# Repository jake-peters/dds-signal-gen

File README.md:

# DDS Signal Generator using AD9834

A signal generator designed around Analog Devices AD9834 DDS chip capable of outputting sinusoidal, triangle and square waves. Output filtering with a 9th order Elliptic filter or 7th order Linear Phase filter. PCB designed in KiCad 6.

V2 version includes update to correct orientation issue with latching relays.

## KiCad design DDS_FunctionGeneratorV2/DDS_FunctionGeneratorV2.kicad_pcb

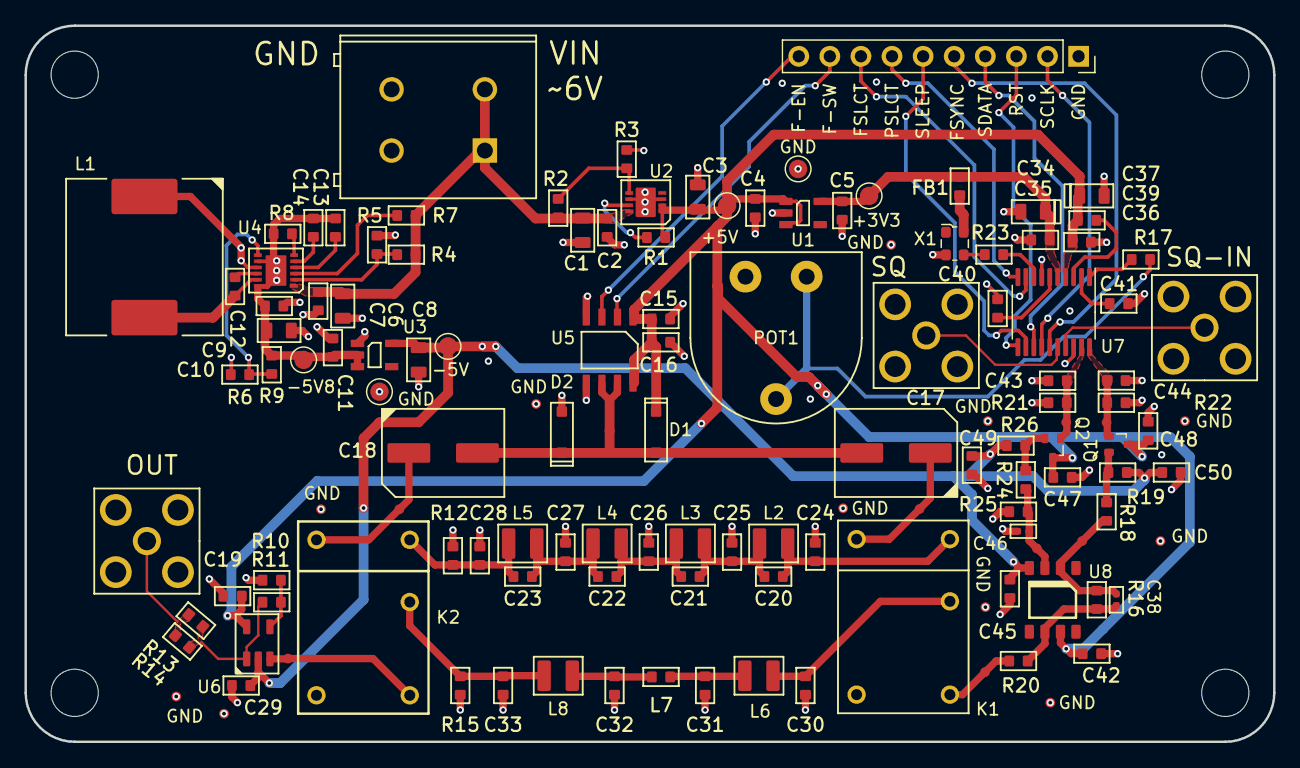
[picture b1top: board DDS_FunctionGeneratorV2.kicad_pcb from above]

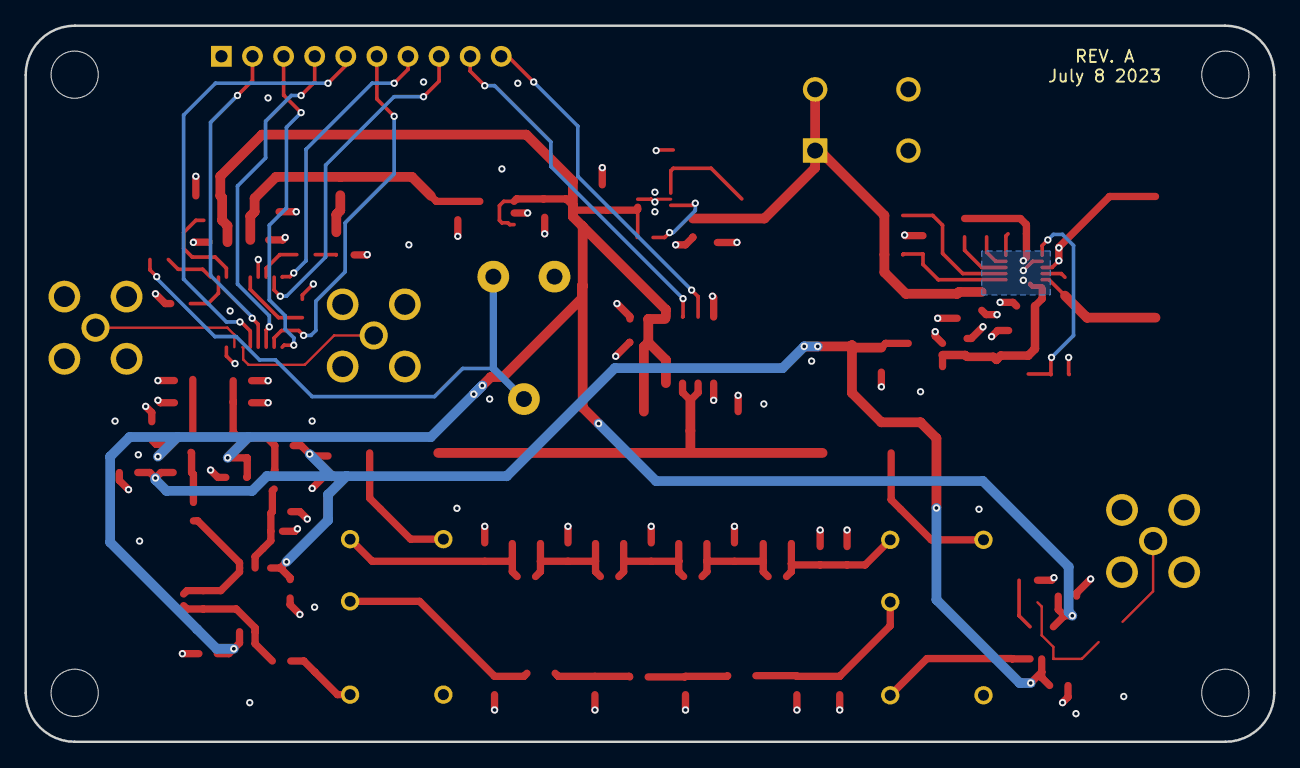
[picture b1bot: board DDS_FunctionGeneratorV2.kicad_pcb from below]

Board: 4 copper layers, 102.0 x 58.5 mm, 137 parts (2 on the bottom side), 59 nets.

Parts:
C1, C3, C6, C8, C10: CAP_0805; SMD_0805
C2, C4, C5, C7, C9, C11, C12, C13, C14, C15, C16, C19, C20, C21, C22, C23, C24, C25, C26, C27, C28, C29, C30, C31, C32, C33, C35, C36, C39, C40, C41, C42, C43, C44, C45, C47, C48, C49, C50: CAP_0603; SMD_0603
C17, C18: 865080345010
C34, C37: CAP_POL_0805; SMD_POL_0805
C38, C46: CAP_0402; SMD_0402
D1, D2: 1N4148W-E3-18; SOD-123
FB1: BEAD_0603; SMD_0603
H1, H2, H3, H4: 0.152_IN_DIA; 0.152_IN_DIA-6-32
J1: 691411410002
J2, J3, J5: SMA_CONN_TH
J4: HEADER_01X10; PinSocket_1x10_P2.54mm_Vertical
K1, K2: DS1E-SL-DC5V
L1: 7447715330
L2, L3, L4, L5, L6, L8: IND_1008; SMD_1008
L7: IND_0603; SMD_0603
POT1: PTN10-E200HB20
Q1, Q2: BFR182W; SOT323_BFR182W
R1, R2, R3, R4, R5, R6, R7, R8, R9, R10, R11, R12, R13, R14, R15, R16, R17, R18, R19, R20, R21, R22, R23, R24, R25, R26: RES_0603; SMD_0603
TP1, TP2, TP3, TP4, TP5, TP6: TestPoint_2.0mm_PAD; TestPoint_Pad_D1.5mm
TP7, TP8, TP9, TP11, TP12, TP13, TP14, TP15, TP16, TP17, TP18, TP20, TP21, TP22, TP23, TP24, TP25, TP26, TP27, TP28, TP29: TestPoint_2.0mm_PAD; TestPoint_Pad_D0.8mm
U1: ADP151AUJZ; TSOT_5Pin
U2: ADP7102; LFCSP_WD_8Pin
U3: ADP7182AUJZ; TSOT_5Pin
U4: MAX17580ATC+; TDFN-EP_12Pin
U5: MCP14A0602-E/SN; SOIC_8Pin
U6: LT1815IS5; TSOT-23_S5-Package
U7: AD9834; TSSOP-20_4.4x6.5mm_P0.65mm
U8: LT1818IS8; S8_Package_LT1818
X1: ECS-TXO-2520MV-500-AY-TR; Oscillator_SMD_ECS_2520MV-xxx-xx-4Pin_2.5x2.0mm

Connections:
+3V3: C5.1, C34.1, C35.2, FB1.1, TP2.1, U1.5 (VOUT), U7.5 (DVDD)
+5V: C3.1, C4.1, C15.1, C16.2, C19.1, C36.2, C37.1, C39.2, C42.2, C47.1, C48.1, D1.1 (K), Q1.3 (C), Q2.3 (C), R1.1, TP1.1, U1.1 (VIN), U1.3 (EN), U2.1 (VOUT), U2.2 (SENSE/ADJ), U5.1 (VDD), U5.8 (VDD), U6.5 (V+), U7.4 (AVDD), U8.7 (V+)
-5V: C8.1, C29.1, C45.2, C49.2, C50.2, R19.2, R26.2, TP5.1, U3.5 (VOUT), U6.2 (V-), U8.4 (V-)
-5V8: C9.1, C10.1, C11.1, C13.2, C14.2, R8.2, R9.2, TP4.1, U3.2 (VIN), U3.3 (EN), U4.8 (SOUT), U4.12 (OUT), U4.13 (EP)
/5V-EN: R2.2, R3.1, U2.5 (EN/UVLO)
/-5V8-EN: R4.1, R5.2, U4.2 (EN/UVLO)
/BST: C12.2, U4.10 (BST)
/DDS/CAP2V5: C40.2, U7.6 (CAP/2.5V)
/DDS/COMP: C39.1, U7.3 (COMP)
/DDS/DDS-VIN: J3.1 (In), U7.17 (VIN)
/DDS/FILT-IN: K1.7, R20.1, TP20.1
/DDS/FS-ADJUST: R17.2, U7.1 (FS_ADJUST)
/DDS/FSELECT: J4.8 (PIN), U7.9 (FSELECT)
/DDS/FSYNC: J4.5 (PIN), U7.15 (~FSYNC)
/DDS/IOUT: C43.1, Q2.1 (B), R21.1, TP22.1, U7.19 (IOUT)
/DDS/IOUTB: C44.1, Q1.1 (B), R22.1, TP17.1, U7.20 (IOUTB)
/DDS/MCLK: R23.1, U7.8 (MCLK)
/DDS/PSELECT: J4.7 (PIN), U7.10 (PSELECT)
/DDS/REFOUT: C41.1, U7.2 (REFOUT)
/DDS/RESET: J4.3 (PIN), U7.11 (RESET)
/DDS/SCLK: J4.2 (PIN), U7.14 (SCLK)
/DDS/SDATA: J4.4 (PIN), U7.13 (SDATA)
/DDS/SIGNBITOUT: J2.1 (In), U7.16 (SIGNBITOUT)
/DDS/SLEEP: J4.6 (PIN), U7.12 (SLEEP)
/FB: R6.2, R9.1, U4.7 (FB)
/LX: C12.1, L1.1, U4.11 (LX)
/Output_Stage/ELLIP-IN: C20.1, C24.1, K1.12, L2.1
/Output_Stage/ELLIP-OUT: C23.2, C28.1, K2.12, L5.2, R12.1
/Output_Stage/FILT-EN: J4.10 (PIN), U5.3 (EN)
/Output_Stage/FILT-OUT: K2.7, TP11.1, U6.3 (+IN)
/Output_Stage/FILT-SWITCH: J4.9 (PIN), U5.2 (VIN)
/Output_Stage/FILTER-SW-IN: C17.2, K1.1, TP7.1
/Output_Stage/FILTER-SW-OUT: C18.2, K2.1, TP9.1
/Output_Stage/LIN-PHASE-IN: C30.1, K1.10, L6.1
/Output_Stage/LIN-PHASE-OUT: C33.1, K2.10, L8.2, R15.1
/Output_Stage/OUT: J5.1 (In), R13.2, R14.2
/PG: R1.2, U2.7 (PG)
/RESET: R7.2, U4.3 (RESET)
/RT/SYNC: R8.1, U4.6 (RT/SYNC)
/SS: C13.1, U4.4 (SS)
/VCC: C14.1, U4.5 (VCC)
/VIN: C1.1, C2.1, C6.1, C7.1, J1.1, R2.1, R4.2, R7.1, U2.8 (VIN), U4.1 (IN)
GND: C1.2, C2.2, C3.2, C4.2, C5.2, C6.2, C7.2, C8.2, C9.2, C10.2, C11.2, C15.2, C16.1, C19.2, C24.2, C25.2, C26.2, C27.2, C28.2, C29.2, C30.2, C31.2, C32.2, C33.2, C34.2, C35.1, C36.1, C37.2, C40.1, C41.2, C42.1, C43.2, C44.2, C45.1, C46.1, C47.2, C48.2, C49.1, C50.1, D2.2 (A), J1.2, J2.2 (GND), J3.2 (GND), J4.1 (PIN), J5.2 (GND), K1.6, K2.6, L1.2, POT1.2, R3.2, R5.1, R6.1, R10.1, R12.2, R15.2, R21.2, R22.2, R25.2, TP3.1, TP6.1, TP12.1, TP13.1, TP14.1, TP15.1, TP16.1, TP24.1, TP25.1, TP26.1, TP27.1, TP28.1, TP29.1, U1.2 (GND), U2.3 (GND), U2.6 (GND), U3.1 (GND), U4.9 (GND), U5.4 (GND), U5.5 (GND), U7.7 (DGND), U7.18 (AGND), X1.2 (GND)
unnamed: C17.1, C18.1, D1.2 (A), D2.1 (K), TP8.1, U5.6 (OUT), U5.7 (OUT)
unnamed: C20.2, C21.1, C25.1, L2.2, L3.1
unnamed: C21.2, C22.1, C26.1, L3.2, L4.1
unnamed: C22.2, C23.1, C27.1, L4.2, L5.1
unnamed: C31.1, L6.2, L7.1
unnamed: C32.1, L7.2, L8.1
unnamed: C38.1, R16.2, R18.1, TP18.1, U8.2 (-IN)
unnamed: C38.2, R16.1, R20.2, U8.6
unnamed: C46.2, R24.1, R25.1, TP23.1, U8.3 (+IN)
unnamed: POT1.1, POT1.3, R17.1
unnamed: Q1.2 (E), R18.2, R19.1
unnamed: Q2.2 (E), R24.2, R26.1
unnamed: R10.2, R11.1, U6.4 (-IN)
unnamed: R11.2, R13.1, R14.1, U6.1
unnamed: R23.2, X1.3 (OUT)
VDD-MCLK: FB1.2, TP21.1, X1.4 (VDD)

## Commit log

2023-07-08 Uploaded DDS Signal Generator KiCad Project
2023-07-08 Library for AD9834 and test program for signal gen
